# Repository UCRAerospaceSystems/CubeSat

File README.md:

# Welcome to the UCR CubeSat project!

## For New Members
### To download this repository:

Install git to your computer: https://git-scm.com/downloads

Open a command line and navigate to a directory of your choice 
(`cd <folder>` on windows/linux, use `ls` to list files and folders in your current directory)

Clone this repo: `git clone https://github.com/UCRAerospaceSystems/CubeSat`

All the files will now be installed to your local machine!

### To commit your changes to this repository:

Ensure that you're up to date with most recent version: `git pull origin master`

Add all files: `git add .`

Commit your changes: `git commit -m "your commit message here"`

Push to the repo: `git push origin master`

## Folder Structure

When adding files to the repo, please sort them in folders ordered by subsystem as well as software used (if CAD files). For example, CAD files of a component designed in Solidworks would go in their own folder within the Solidworks folder.

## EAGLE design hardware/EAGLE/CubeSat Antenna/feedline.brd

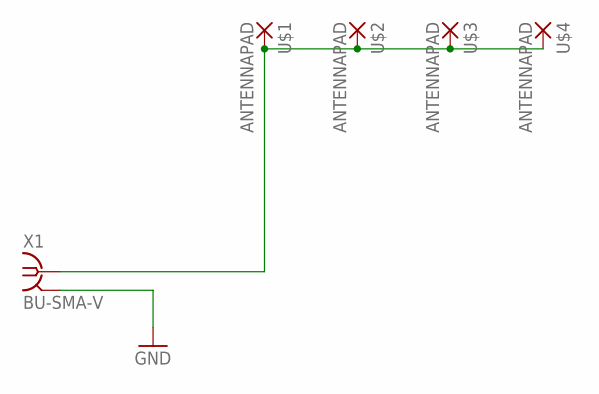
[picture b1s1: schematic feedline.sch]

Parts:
U$1, U$2, U$3, U$4: ANTENNAPAD; CMMOUNTPAD
X1: BU-SMA-V

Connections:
FEED: U$1.P$1, U$2.P$1, U$3.P$1, U$4.P$1, X1.1
GND: X1.2, X1.3 (2), X1.4 (2), X1.5 (2)

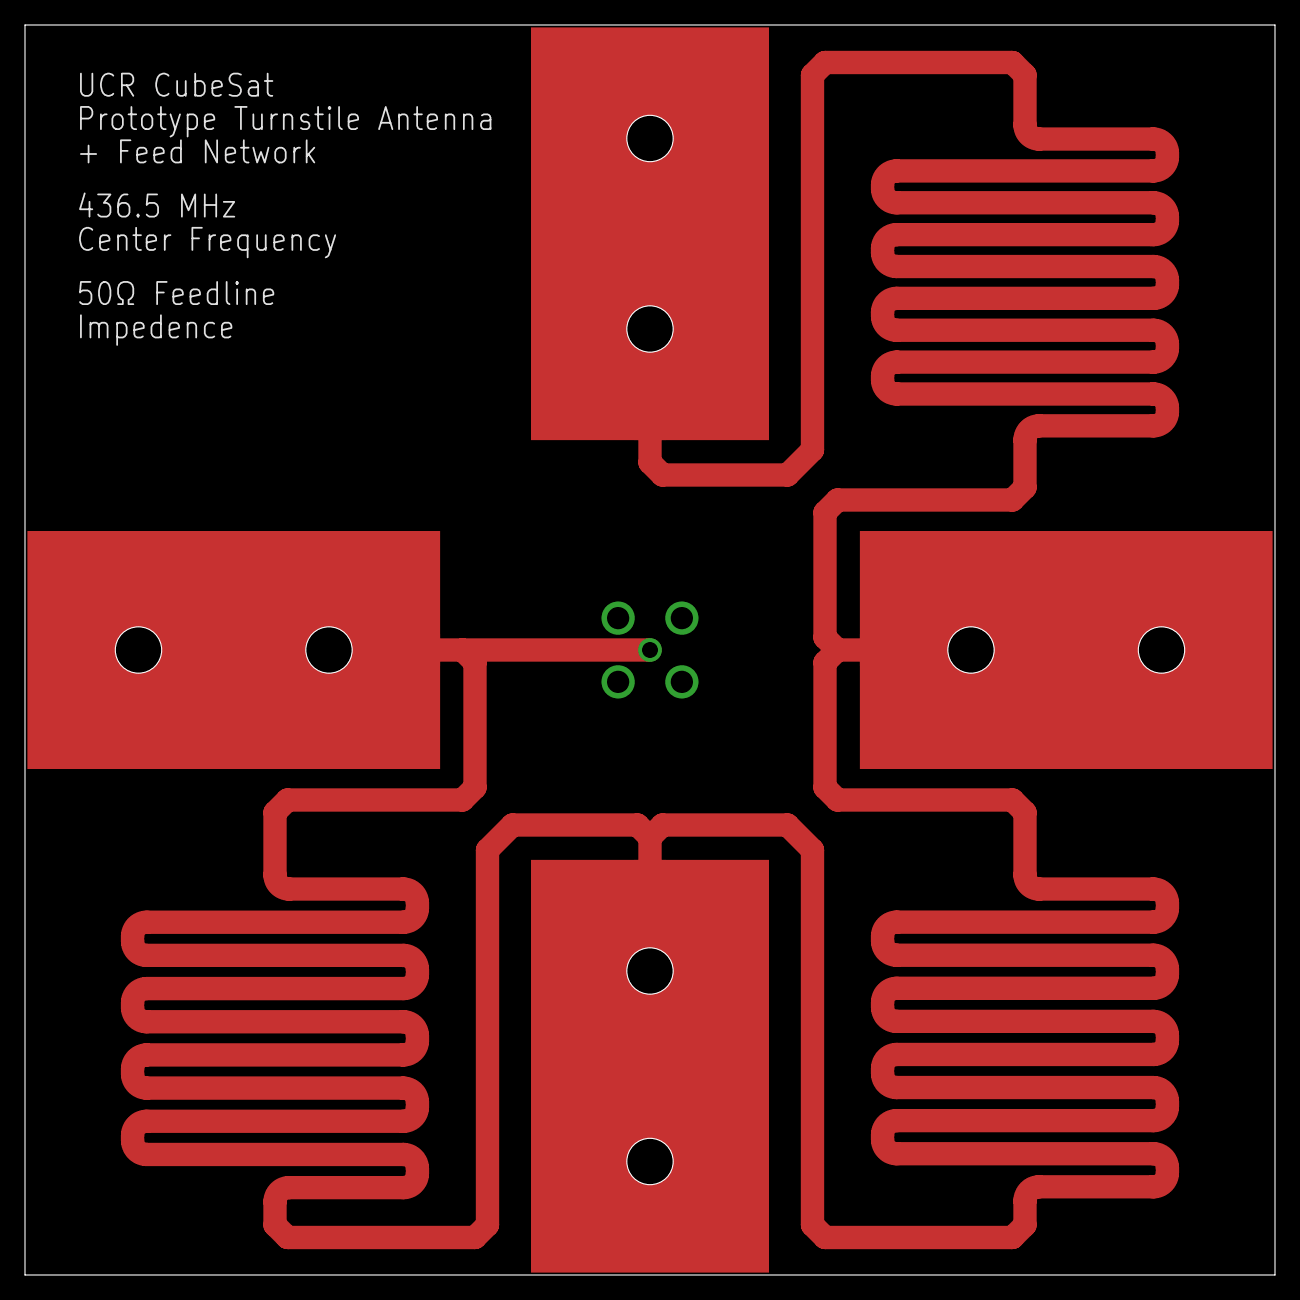
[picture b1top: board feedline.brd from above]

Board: 2 copper layers, 100.0 x 100.0 mm, 5 parts (1 on the bottom side), 2 nets.

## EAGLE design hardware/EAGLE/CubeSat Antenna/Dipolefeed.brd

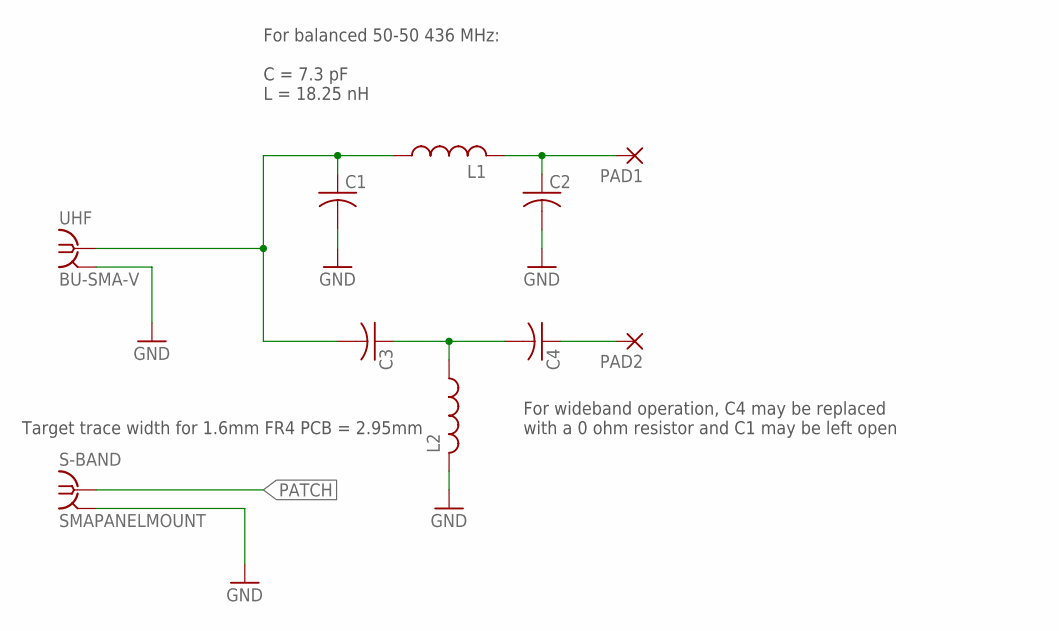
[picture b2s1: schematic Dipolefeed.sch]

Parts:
C1, C2, C3, C4: C-USC1608; C1608
L1, L2: L-USL2012C; L2012C
PAD1: 0; CMMOUNTPAD2
PAD2: 180; CMMOUNTPAD2
S-BAND: SMAPANELMOUNT; PANELSMA
UHF: BU-SMA-V

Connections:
GND: C1.2, C2.2, L2.2, S-BAND.P$2 (2), S-BAND.P$3 (2), UHF.2, UHF.3 (2), UHF.4 (2), UHF.5 (2)
unnamed: C2.1, L1.2, PAD1.P$1
unnamed: C3.1, C4.2, L2.1
unnamed: C4.1, PAD2.P$1
unnamed: C1.1, C3.2, L1.1, UHF.1
PATCH: S-BAND.P$1 (1)

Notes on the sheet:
For balanced 50-50 436 MHz: C = 7.3 pF L = 18.25 nH
For wideband operation, C4 may be replaced with a 0 ohm resistor and C1 may be left open
Target trace width for 1.6mm FR4 PCB = 2.95mm

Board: 2 copper layers, 10 parts (2 on the bottom side), 5 nets, no tracks yet.

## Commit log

2020-10-12 pull request test
2020-10-12 added EAGLE files for antenna board
2020-10-13 this this a test
2020-10-13 Updated test file.txt
2020-10-13 Uploading commit
2020-10-13 New commit
2020-10-13 name
2020-10-15 update README.md again
2020-10-20 Solid Works Files structure
2020-10-20 rearranged folders
2020-11-09 Add files via upload
    a very rough file
2021-01-01 added sail watchdog test code
2021-01-01 more sail test code
2021-01-05 added basic ADC and PWM test code
2021-02-23 added antenna and sail mechanism assemblies
2021-04-23 completed first mock CAD
2021-05-12 Added initial communications files
2021-09-22 update to 3U
2021-10-26 add latest sail code
